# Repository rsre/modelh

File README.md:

# Model H
Replacement Model M controller board

Still a work in progress.

## Part list

### 16 + 8 + 4 Pin Ribbons
* CONN FFC VERT 16POS 2.54MM PCB - https://www.digikey.com/products/en?keywords=A144434-ND
* CONN FFC VERT 8POS 2.54MM PCB - https://www.digikey.com/products/en?keywords=5-520315-8-ND
* CONN FFC VERT 4POS 2.54MM PCB - https://www.digikey.com/products/en?keywords=A123169-ND

### 16 + 12 Pin Ribbons
* CONN FFC VERT 16POS 2.54MM PCB - https://www.digikey.com/products/en?keywords=A144434-ND
* CONN FFC VERT 12POS 2.54MM PCB - https://www.digikey.com/products/en?keywords=A123179-ND

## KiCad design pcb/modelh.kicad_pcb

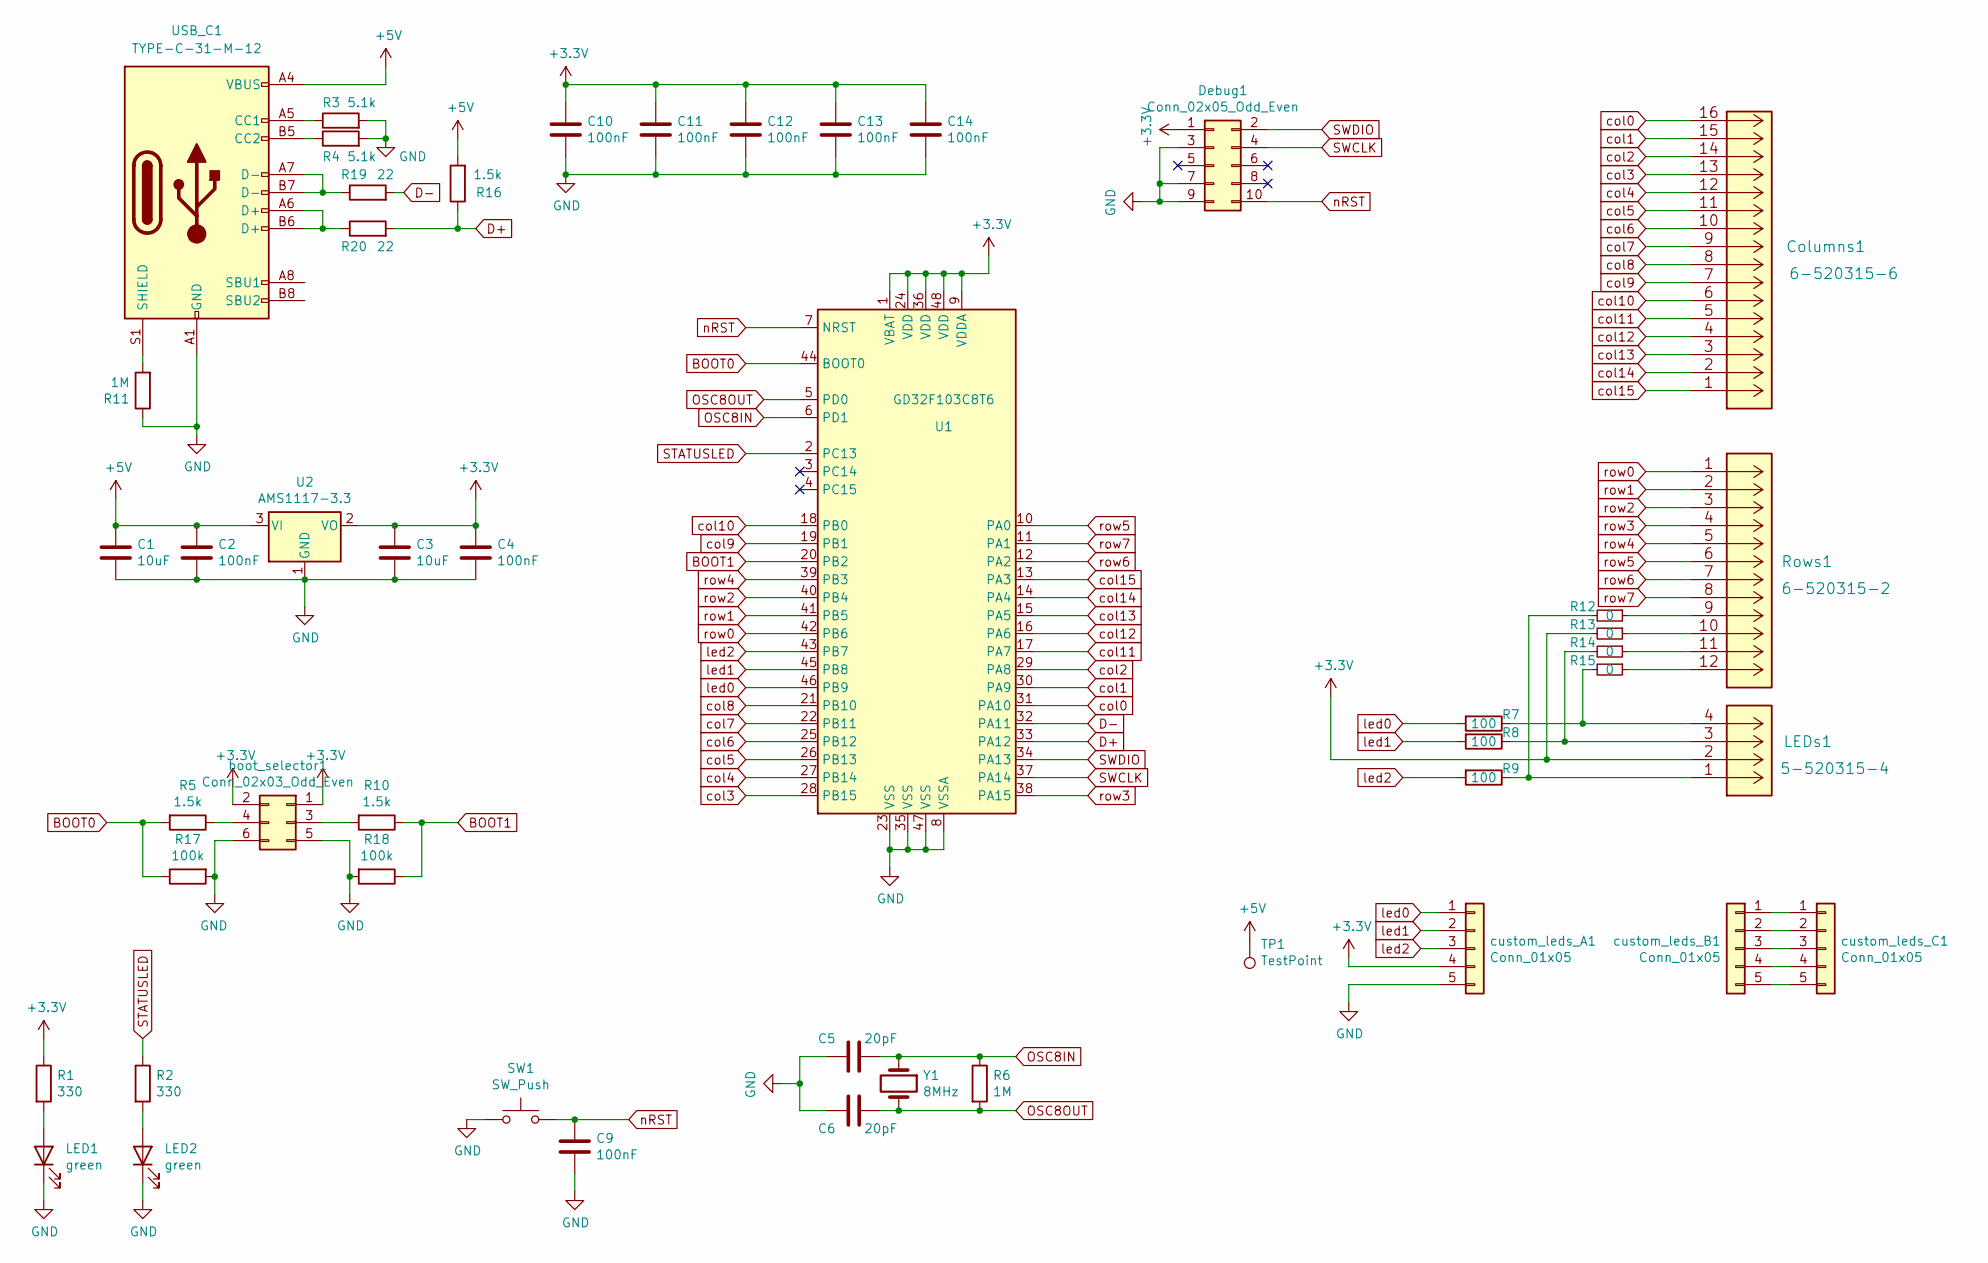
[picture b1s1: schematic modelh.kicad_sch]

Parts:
C1, C3: 10uF; C_0603_1608Metric; LCSC C19702
C2, C4, C9, C10, C11, C12, C13, C14: 100nF; C_0402_1005Metric; LCSC C1525
C5, C6: 20pF; C_0603_1608Metric; LCSC C1653
Columns1: 6-520315-6; CONN_6-520315-6_TYC
Debug1: Conn_02x05_Odd_Even; IDC-Header_2x05_P2.54mm_Vertical
LED1, LED2: green; LED_0805_2012Metric; LCSC C2297
LEDs1: 5-520315-4; CONN_5-520315-4_TYC
R1, R2: 330; R_0603_1608Metric; LCSC C23138
R3, R4: 5.1k; R_0603_1608Metric; LCSC C23345
R5, R10, R16: 1.5k; R_0603_1608Metric; LCSC C22843
R6: 1M; R_0603_1608Metric; LCSC C22935
R7, R8, R9: 100; R_0805_2012Metric; LCSC C17408
R11: 1M; R_0603_1608Metric; LCSC C26098
R12, R13, R14, R15: 0; R_0805_2012Metric_Pad1.15x1.40mm_HandSolder; LCSC C17477
R17, R18: 100k; R_0603_1608Metric; LCSC C25803
R19, R20: 22; R_0603_1608Metric; LCSC C23345
Rows1: 6-520315-2; CONN_6-520315-2_TYC
SW1: SW_Push; SW_SPST_EVPBF; LCSC C318888
TP1: TestPoint; TestPoint_THTPad_D1.5mm_Drill0.7mm
U1: GD32F103C8T6; LQFP-48_7x7mm_P0.5mm; LCSC C77994
U2: AMS1117-3.3; SOT-223-3_TabPin2; LCSC C6186
USB_C1: TYPE-C-31-M-12; USB_C_Receptacle_HRO_TYPE-C-31-M-12; LCSC C165948
Y1: 8MHz; Crystal_SMD_5032-2Pin_5.0x3.2mm; LCSC C115962
boot_selector1: Conn_02x03_Odd_Even; PinHeader_2x03_P2.54mm_Vertical
custom_leds_A1: Conn_01x05; PinSocket_1x05_P2.54mm_Vertical
custom_leds_B1: Conn_01x05; PinSocket_1x05_P2.54mm_Vertical
custom_leds_C1: Conn_01x05; PinSocket_1x05_P2.54mm_Vertical

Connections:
+3V3: C3.1, C4.1, C10.1, C11.1, C12.1, C13.1, C14.1, Debug1.1, LEDs1.2, R1.1, R13.2, U1.1 (VBAT), U1.9 (VDDA), U1.24 (VDD), U1.36 (VDD), U1.48 (VDD), U2.2 (VO), boot_selector1.1, boot_selector1.2, custom_leds_A1.4
+5V: C1.1, C2.1, R16.2, TP1.1, U2.3 (VI), USB_C1.A4 (VBUS), USB_C1.A9 (VBUS), USB_C1.B4 (VBUS), USB_C1.B9 (VBUS)
BOOT0: R5.2, R17.1, U1.44 (BOOT0)
BOOT1: R10.1, R18.1, U1.20 (PB2)
D-: R19.2, U1.32 (PA11)
GND: C1.2, C2.2, C3.2, C4.2, C5.2, C6.2, C9.2, C10.2, C11.2, C12.2, C13.2, C14.2, Debug1.3, Debug1.7, Debug1.9, LED1.1 (K), LED2.1 (K), R3.2, R4.2, R11.1, R17.2, R18.2, SW1.1, U1.8 (VSSA), U1.23 (VSS), U1.35 (VSS), U1.47 (VSS), U2.1 (GND), USB_C1.A1 (GND), USB_C1.A12 (GND), USB_C1.B1 (GND), USB_C1.B12 (GND), boot_selector1.5, boot_selector1.6, custom_leds_A1.5
unnamed: LED1.2 (A), R1.2
unnamed: LED2.2 (A), R2.2
unnamed: LEDs1.1, R9.1, R12.2
unnamed: LEDs1.3, R8.1, R14.2
unnamed: LEDs1.4, R7.1, R15.2
unnamed: R3.1, USB_C1.A5 (CC1)
unnamed: R4.1, USB_C1.B5 (CC2)
unnamed: R5.1, boot_selector1.4
unnamed: R10.2, boot_selector1.3
unnamed: R11.2, USB_C1.S1 (SHIELD)
unnamed: R12.1, Rows1.9
unnamed: R13.1, Rows1.10
unnamed: R14.1, Rows1.11
unnamed: R15.1, Rows1.12
unnamed: R19.1, USB_C1.A7 (D-), USB_C1.B7 (D-)
unnamed: custom_leds_B1.1, custom_leds_C1.1
unnamed: custom_leds_B1.2, custom_leds_C1.2
unnamed: custom_leds_B1.3, custom_leds_C1.3
unnamed: custom_leds_B1.4, custom_leds_C1.4
unnamed: custom_leds_B1.5, custom_leds_C1.5
OSC8IN: C5.1, R6.1, U1.6 (PD1), Y1.1
OSC8OUT: C6.1, R6.2, U1.5 (PD0), Y1.2
STATUSLED: R2.1, U1.2 (PC13)
SWCLK: Debug1.4, U1.37 (PA14)
SWDIO: Debug1.2, U1.34 (PA13)
col0: Columns1.16, U1.31 (PA10)
col1: Columns1.15, U1.30 (PA9)
col2: Columns1.14, U1.29 (PA8)
col3: Columns1.13, U1.28 (PB15)
col4: Columns1.12, U1.27 (PB14)
col5: Columns1.11, U1.26 (PB13)
col6: Columns1.10, U1.25 (PB12)
col7: Columns1.9, U1.22 (PB11)
col8: Columns1.8, U1.21 (PB10)
col9: Columns1.7, U1.19 (PB1)
col10: Columns1.6, U1.18 (PB0)
col11: Columns1.5, U1.17 (PA7)
col12: Columns1.4, U1.16 (PA6)
col13: Columns1.3, U1.15 (PA5)
col14: Columns1.2, U1.14 (PA4)
col15: Columns1.1, U1.13 (PA3)
led0: R7.2, U1.46 (PB9), custom_leds_A1.1
led1: R8.2, U1.45 (PB8), custom_leds_A1.2
led2: R9.2, U1.43 (PB7), custom_leds_A1.3
nRST: C9.1, Debug1.10, SW1.2, U1.7 (NRST)
row0: Rows1.1, U1.42 (PB6)
row1: Rows1.2, U1.41 (PB5)
row2: Rows1.3, U1.40 (PB4)
row3: Rows1.4, U1.38 (PA15)
row4: Rows1.5, U1.39 (PB3)
row5: Rows1.6, U1.10 (PA0)
row6: Rows1.7, U1.12 (PA2)
row7: Rows1.8, U1.11 (PA1)

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
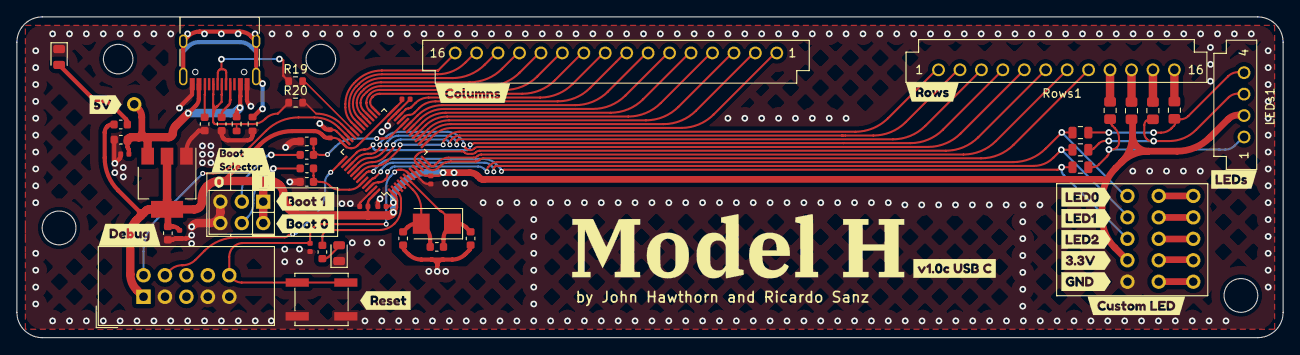
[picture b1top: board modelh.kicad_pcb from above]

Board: 2 copper layers, 150.0 x 38.0 mm, 70 parts (0 on the bottom side), 61 nets.

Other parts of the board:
HOLE1, HOLE2: MountingHole_3.5mm
HOLE3, HOLE4: MountingHole_4mm
MODELH_LOGO: LOGO; modelh_logo
kibuzzard-61E6F38C: G***; kibuzzard-61E6F38C
kibuzzard-61E6F754: G***; kibuzzard-61E6F754
kibuzzard-61E18CD3: G***; kibuzzard-61E18CD3
kibuzzard-61E18CE3: G***; kibuzzard-61E18CE3
kibuzzard-61E67D4F: G***; kibuzzard-61E67D4F
kibuzzard-61E83ADE: G***; kibuzzard-61E83ADE
kibuzzard-61E84BB4: G***; kibuzzard-61E84BB4
kibuzzard-61E84BBD: G***; kibuzzard-61E84BBD
kibuzzard-61E846DB: G***; kibuzzard-61E846DB
kibuzzard-61E1917D: G***; kibuzzard-61E1917D
kibuzzard-61E1928B: G***; kibuzzard-61E1928B
kibuzzard-61E1934D: G***; kibuzzard-61E1934D
kibuzzard-61E1935A: G***; kibuzzard-61E1935A
kibuzzard-61E19345: G***; kibuzzard-61E19345
kibuzzard-61E19354: G***; kibuzzard-61E19354
kibuzzard-61E19361: G***; kibuzzard-61E19361
kibuzzard-61E19404: G***; kibuzzard-61E19404

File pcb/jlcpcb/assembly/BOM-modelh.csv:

Comment,Designator,Footprint,LCSC
1M,R11,R_0603_1608Metric, C26098
8MHz,Y1,Crystal_SMD_5032-2Pin_5.0x3.2mm,C115962
100nF,"C10,C11,C12,C13,C14,C2,C4,C9",C_0402_1005Metric,C1525
20pF,"C5,C6",C_0603_1608Metric,C1653
TYPE-C-31-M-12,USB_C1,USB_C_Receptacle_HRO_TYPE-C-31-M-12,C165948
100,"R7,R8,R9",R_0805_2012Metric,C17408
0,"R12,R13,R14,R15",R_0805_2012Metric_Pad1.15x1.40mm_HandSolder,C17477
10uF,"C1,C3",C_0603_1608Metric,C19702
1.5k,"R10,R16,R5",R_0603_1608Metric,C22843
1M,R6,R_0603_1608Metric,C22935
green,"LED1,LED2",LED_0805_2012Metric,C2297
330,"R1,R2",R_0603_1608Metric,C23138
22,"R3,R4",R_0603_1608Metric,C23345
100k,"R17,R18",R_0603_1608Metric,C25803
SW_Push,SW1,SW_SPST_EVPBF,C318888
AMS1117-3.3,U2,SOT-223-3_TabPin2,C6186
GD32F103C8T6,U1,LQFP-48_7x7mm_P0.5mm,C77994
Conn_02x05_Odd_Even,Debug1,IDC-Header_2x05_P2.54mm_Vertical,
Conn_02x03_Odd_Even,boot_selector1,PinHeader_2x03_P2.54mm_Vertical,
Conn_01x05,custom_leds_C1,PinSocket_1x05_P2.54mm_Vertical,
Conn_01x05,custom_leds_B1,PinSocket_1x05_P2.54mm_Vertical,
Conn_01x05,custom_leds_A1,PinSocket_1x05_P2.54mm_Vertical,
TestPoint,TP1,TestPoint_THTPad_D1.5mm_Drill0.7mm,
5-520315-4,LEDs1,CONN_5-520315-4_TYC,
6-520315-2,Rows1,CONN_6-520315-2_TYC,
6-520315-6,Columns1,CONN_6-520315-6_TYC,

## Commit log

2022-01-14 Substitutes USB B connector with USB C connector
2022-01-14 Updates 3D models and moves USB closer to edge
2022-01-14 Fixes
2022-01-14 Updates connector footprint
2022-01-14 Adds 3D files to repository
2022-01-14 Updates shim for USB C
2022-01-17 Remove old gerbers
2022-01-17 Remove old backups
2022-01-17 Renames a few components
2022-01-17 Generate JLC PCB files
2022-01-17 Removes JLC PCB production files
2022-01-17 Updates some components
2022-01-19 Updates TE connectors footprints
2022-01-19 Updates silkscreen to make clear boot selector
2022-01-19 Adjust footprints
2022-01-19 JLC PCB Production files
2022-02-09 Adds hatched pattern to groundplane
2022-02-09 Places USB C connector completely inside the board
2022-02-26 Adds missing 1.5k pullup resistor to USB D+ line
2022-12-25 Add gerbers
2022-12-25 Update schematics and pcb
2022-12-25 Add matrix pictures for reverse engineering
2022-12-25 Add qmk config
2022-12-25 Add firmware documentation
2022-12-25 Upgrade to QMK 0.19.5
2022-12-25 Update keymaps
2022-12-25 Update gitignore to be the standard kicad one
2022-12-25 Update README to reflect all different connector requirements
2022-12-27 Add proper CC resistors for USB C
2022-12-27 Move pull up in front of 0 ohm resistors
